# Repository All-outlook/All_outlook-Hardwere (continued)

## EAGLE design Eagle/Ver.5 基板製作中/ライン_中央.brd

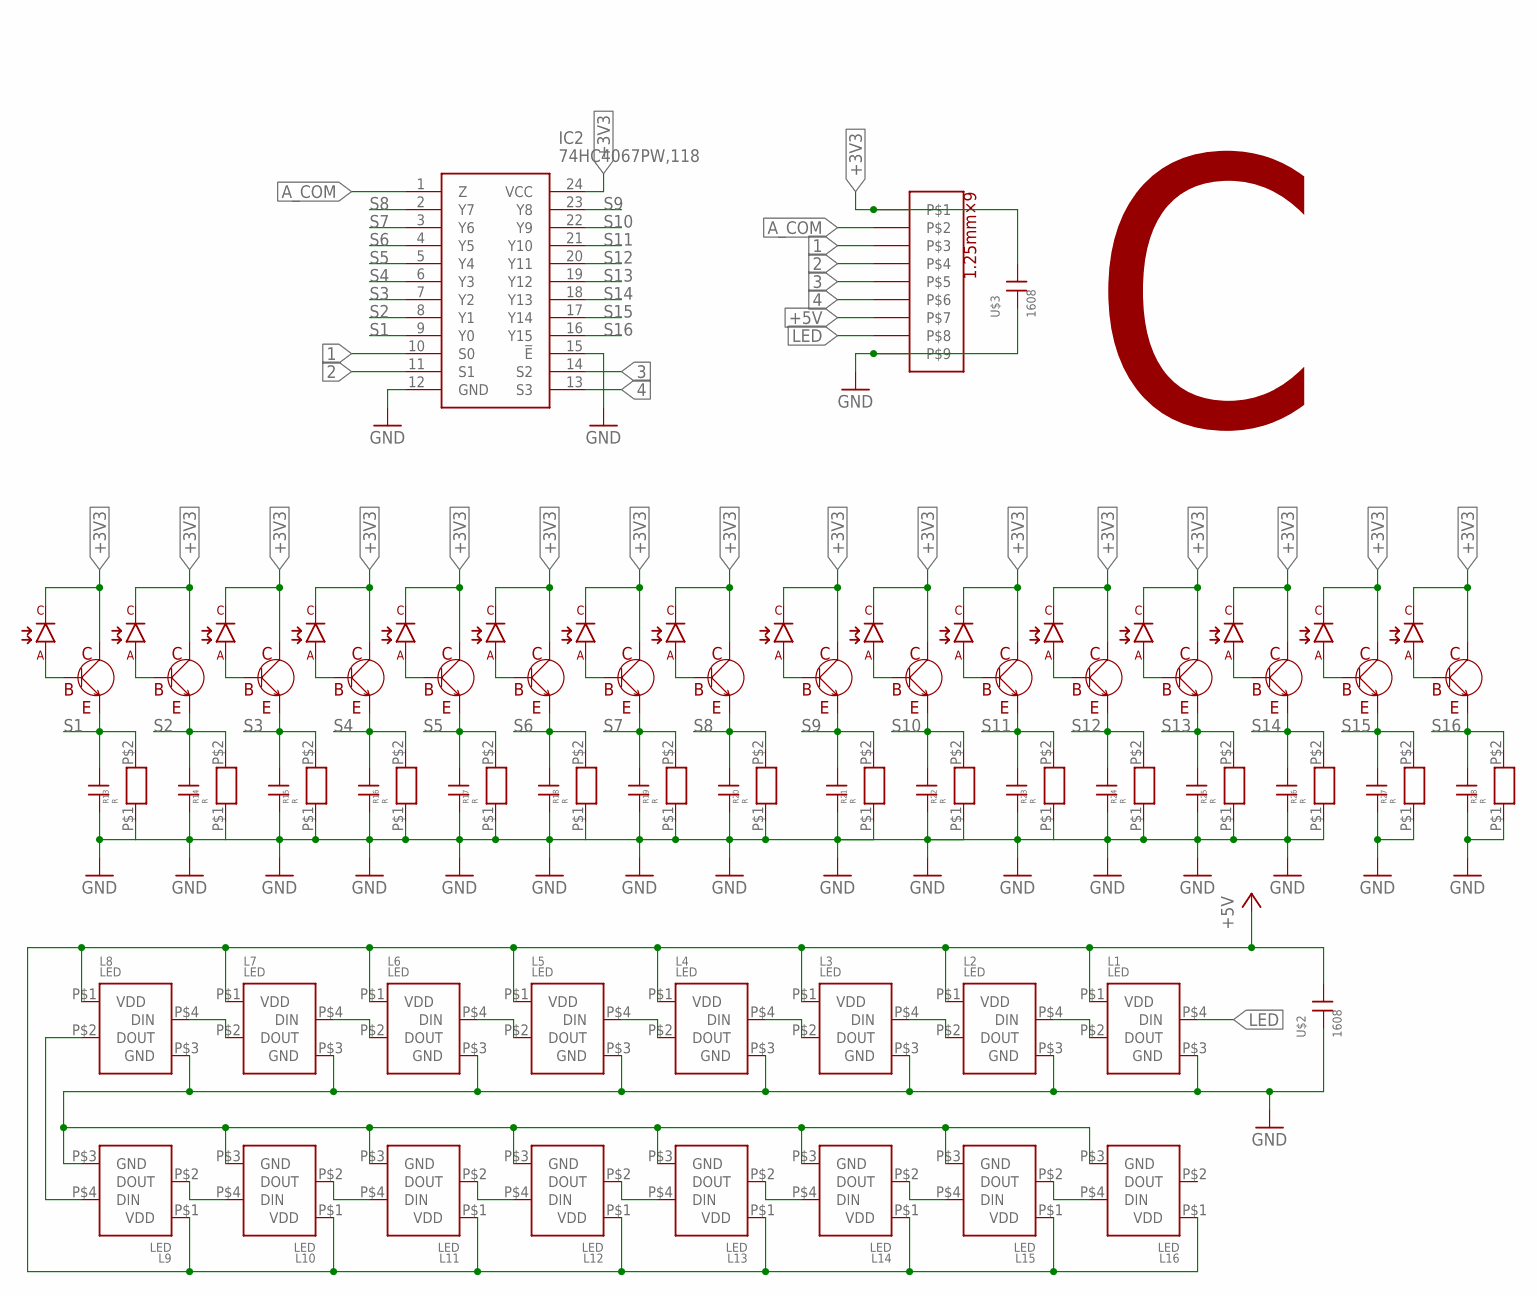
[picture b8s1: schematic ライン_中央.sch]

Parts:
C13, C14, C15, C16, C17, C18, C19, C20, C21, C22, C23, C24, C25, C26, C27, C28: 1608; CON
IC2: 74HC4067PW,118; SOP65P640X110-24N
L1, L2, L3, L4, L5, L6, L7, L8, L9, L10, L11, L12, L13, L14, L15, L16: LED
P1, P2, P3, P4, P5, P6, P7, P8, P9, P10, P11, P12, P13, P14, P15, P16: フォトダイオード
R13, R14, R15, R16, R17, R18, R19, R20, R21, R22, R23, R24, R25, R26, R27, R28: R; 1608
T1, T2, T3, T4, T5, T6, T7, T8, T9, T10, T11, T12, T13, T14, T15, T16: 2CS2712; TRANS_SSM3J325F,LF
U$1: 1MMCON
U$2, U$3: 1608; CON

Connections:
1: IC2.10 (S0), U$1.P$3
2: IC2.11 (S1), U$1.P$4
3: IC2.14 (S2), U$1.P$5
4: IC2.13 (S3), U$1.P$6
+3V3: IC2.24 (VCC), P1.C, P2.C, P3.C, P4.C, P5.C, P6.C, P7.C, P8.C, P9.C, P10.C, P11.C, P12.C, P13.C, P14.C, P15.C, P16.C, T1.C, T2.C, T3.C, T4.C, T5.C, T6.C, T7.C, T8.C, T9.C, T10.C, T11.C, T12.C, T13.C, T14.C, T15.C, T16.C, U$1.P$1, U$3.P$1 (1)
+5V: L1.P$1 (VDD), L2.P$1 (VDD), L3.P$1 (VDD), L4.P$1 (VDD), L5.P$1 (VDD), L6.P$1 (VDD), L7.P$1 (VDD), L8.P$1 (VDD), L9.P$1 (VDD), L10.P$1 (VDD), L11.P$1 (VDD), L12.P$1 (VDD), L13.P$1 (VDD), L14.P$1 (VDD), L15.P$1 (VDD), L16.P$1 (VDD), U$1.P$7, U$2.P$1 (1)
A_COM: IC2.1 (Z), U$1.P$2
GND: C13.P$2 (2), C14.P$2 (2), C15.P$2 (2), C16.P$2 (2), C17.P$2 (2), C18.P$2 (2), C19.P$2 (2), C20.P$2 (2), C21.P$2 (2), C22.P$2 (2), C23.P$2 (2), C24.P$2 (2), C25.P$2 (2), C26.P$2 (2), C27.P$2 (2), C28.P$2 (2), IC2.12 (GND), IC2.15 (!E), L1.P$3 (GND), L2.P$3 (GND), L3.P$3 (GND), L4.P$3 (GND), L5.P$3 (GND), L6.P$3 (GND), L7.P$3 (GND), L8.P$3 (GND), L9.P$3 (GND), L10.P$3 (GND), L11.P$3 (GND), L12.P$3 (GND), L13.P$3 (GND), L14.P$3 (GND), L15.P$3 (GND), L16.P$3 (GND), R13.P$1, R14.P$1, R15.P$1, R16.P$1, R17.P$1, R18.P$1, R19.P$1, R20.P$1, R21.P$1, R22.P$1, R23.P$1, R24.P$1, R25.P$1, R26.P$1, R27.P$1, R28.P$1, U$1.P$9, U$2.P$2 (2), U$3.P$2 (2)
LED: L1.P$4 (DIN), U$1.P$8
unnamed: P1.A, T1.B
unnamed: P2.A, T2.B
unnamed: P3.A, T3.B
unnamed: P4.A, T4.B
unnamed: P5.A, T5.B
unnamed: P6.A, T6.B
unnamed: P7.A, T7.B
unnamed: P8.A, T8.B
unnamed: P9.A, T9.B
unnamed: P10.A, T10.B
unnamed: P11.A, T11.B
unnamed: P12.A, T12.B
unnamed: P13.A, T13.B
unnamed: P14.A, T14.B
unnamed: P15.A, T15.B
unnamed: P16.A, T16.B
unnamed: L15.P$2 (DOUT), L16.P$4 (DIN)
unnamed: L14.P$2 (DOUT), L15.P$4 (DIN)
unnamed: L11.P$2 (DOUT), L12.P$4 (DIN)
unnamed: L10.P$2 (DOUT), L11.P$4 (DIN)
unnamed: L9.P$2 (DOUT), L10.P$4 (DIN)
unnamed: L13.P$2 (DOUT), L14.P$4 (DIN)
unnamed: L12.P$2 (DOUT), L13.P$4 (DIN)
unnamed: L7.P$2 (DOUT), L8.P$4 (DIN)
unnamed: L6.P$2 (DOUT), L7.P$4 (DIN)
unnamed: L3.P$2 (DOUT), L4.P$4 (DIN)
unnamed: L2.P$2 (DOUT), L3.P$4 (DIN)
unnamed: L1.P$2 (DOUT), L2.P$4 (DIN)
unnamed: L5.P$2 (DOUT), L6.P$4 (DIN)
unnamed: L4.P$2 (DOUT), L5.P$4 (DIN)
unnamed: L8.P$2 (DOUT), L9.P$4 (DIN)
S1: C13.P$1 (1), IC2.9 (Y0), R13.P$2, T1.E
S2: C14.P$1 (1), IC2.8 (Y1), R14.P$2, T2.E
S3: C15.P$1 (1), IC2.7 (Y2), R15.P$2, T3.E
S4: C16.P$1 (1), IC2.6 (Y3), R16.P$2, T4.E
S5: C17.P$1 (1), IC2.5 (Y4), R17.P$2, T5.E
S6: C18.P$1 (1), IC2.4 (Y5), R18.P$2, T6.E
S7: C19.P$1 (1), IC2.3 (Y6), R19.P$2, T7.E
S8: C20.P$1 (1), IC2.2 (Y7), R20.P$2, T8.E
S9: C21.P$1 (1), IC2.23 (Y8), R21.P$2, T9.E
S10: C22.P$1 (1), IC2.22 (Y9), R22.P$2, T10.E
S11: C23.P$1 (1), IC2.21 (Y10), R23.P$2, T11.E
S12: C24.P$1 (1), IC2.20 (Y11), R24.P$2, T12.E
S13: C25.P$1 (1), IC2.19 (Y12), R25.P$2, T13.E
S14: C26.P$1 (1), IC2.18 (Y13), R26.P$2, T14.E
S15: C27.P$1 (1), IC2.17 (Y14), R27.P$2, T15.E
S16: C28.P$1 (1), IC2.16 (Y15), R28.P$2, T16.E

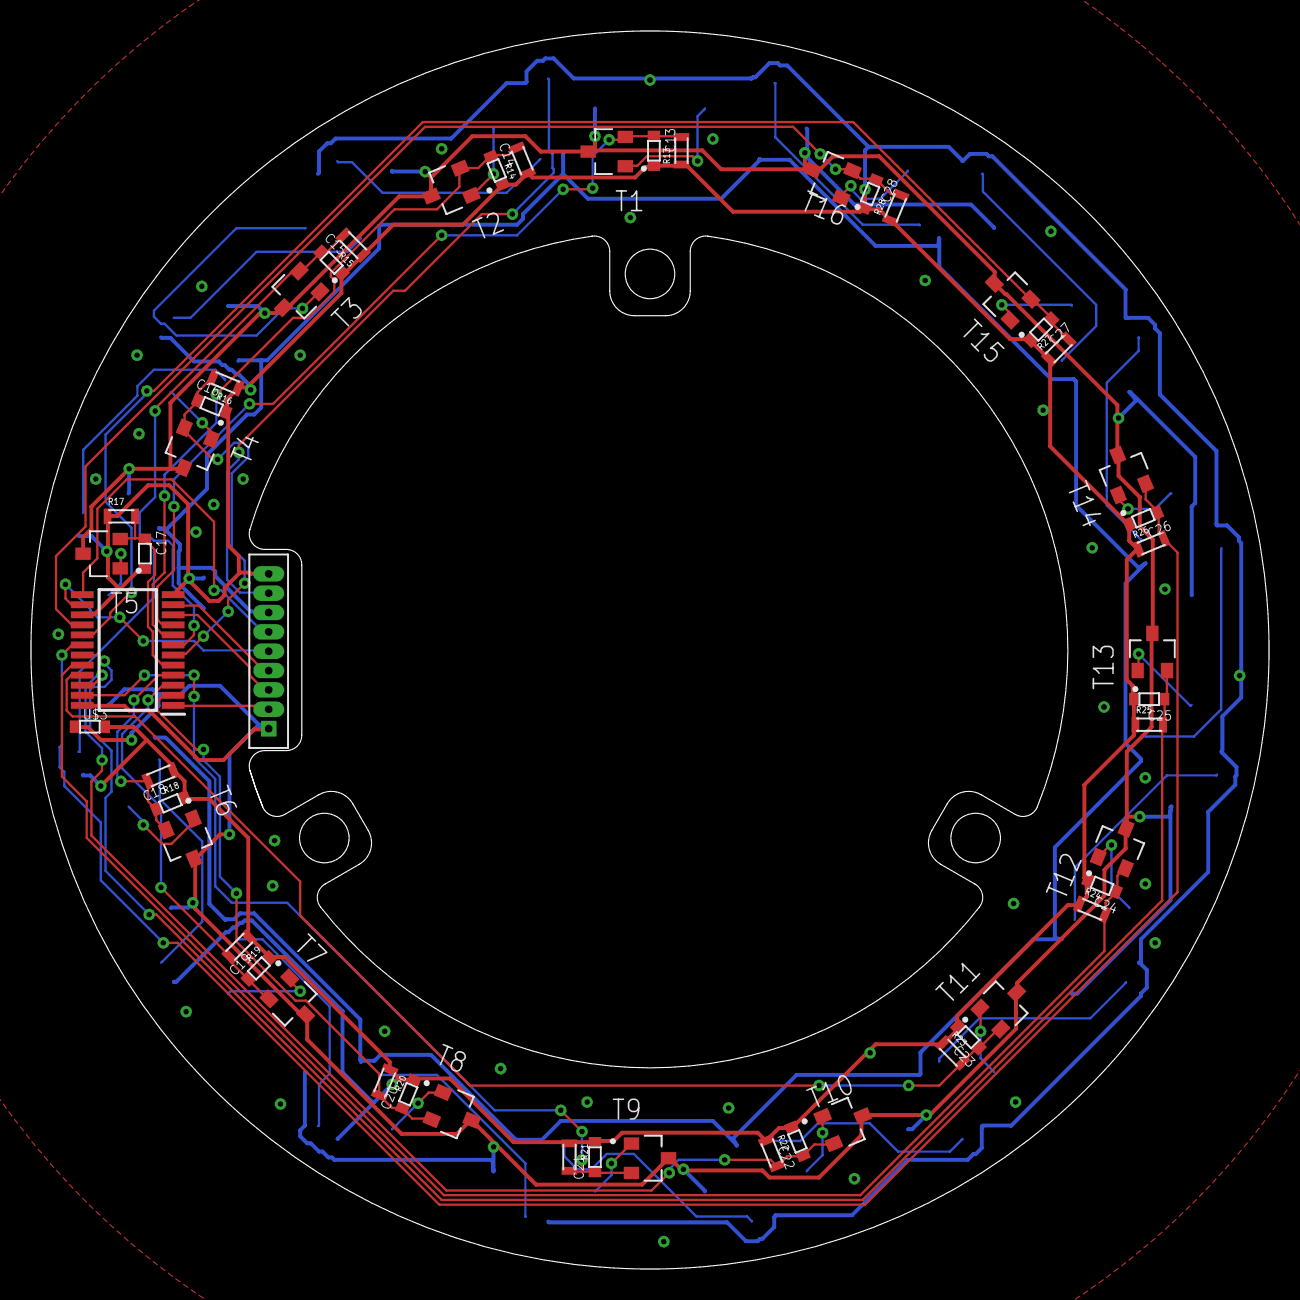
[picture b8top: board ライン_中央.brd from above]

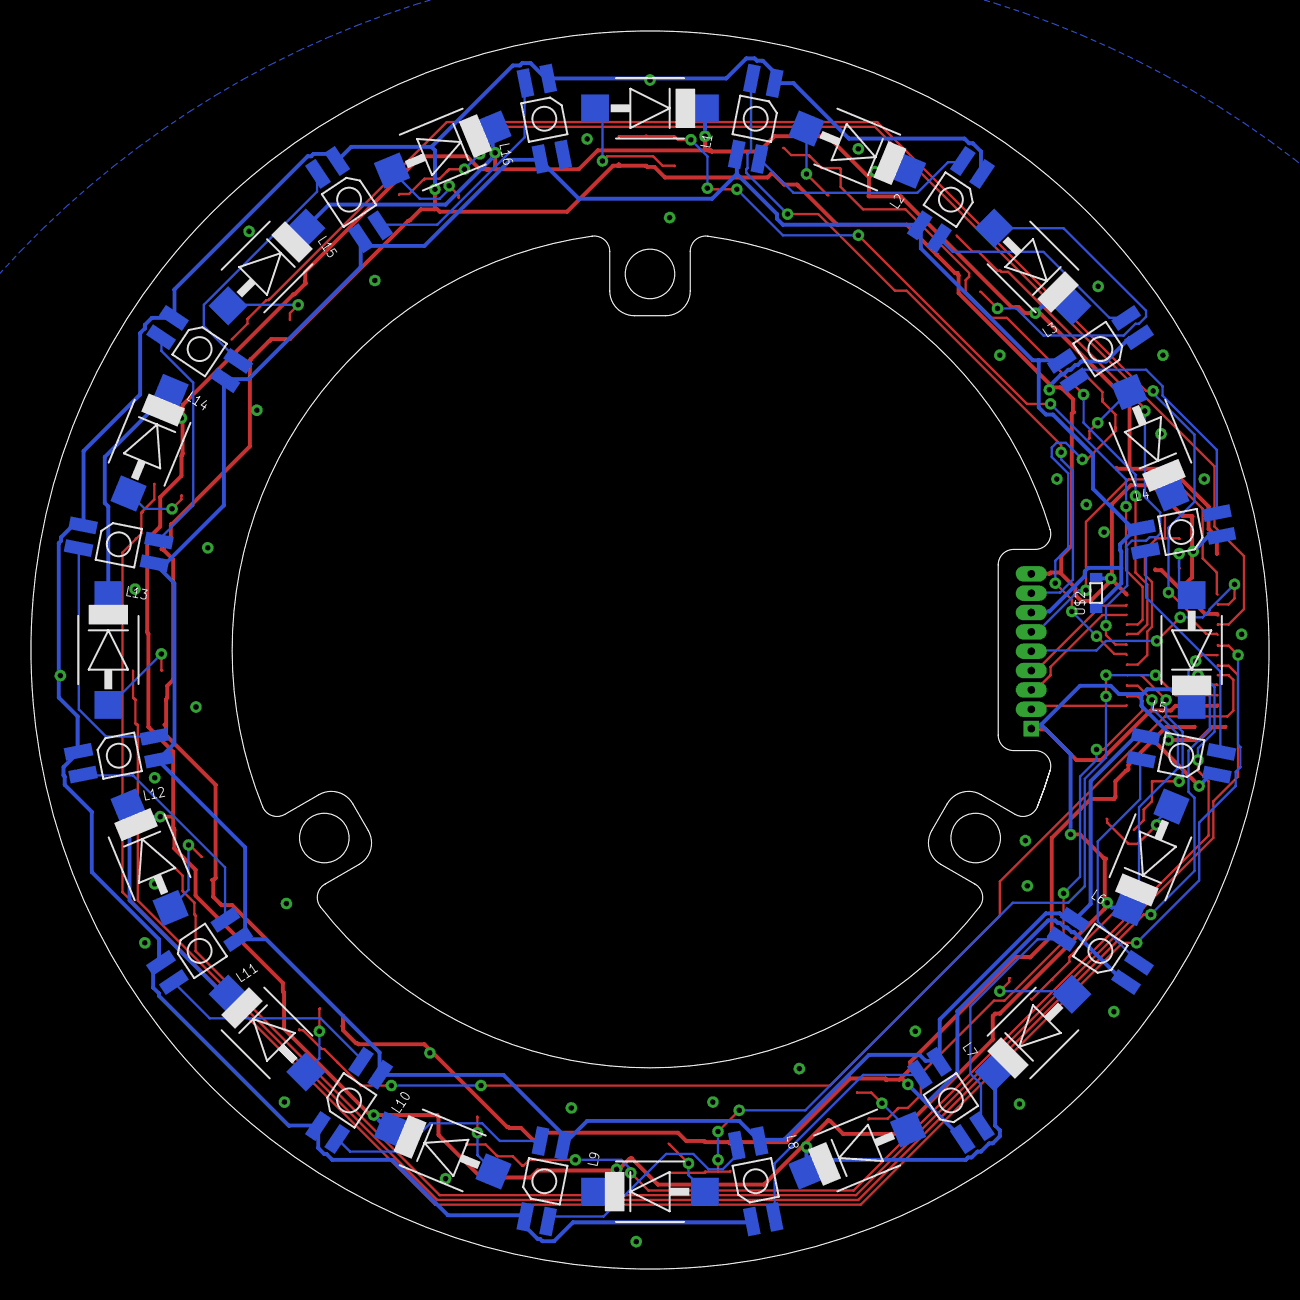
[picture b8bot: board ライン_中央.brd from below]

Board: 2 copper layers, 80.0 x 80.0 mm, 84 parts (33 on the bottom side), 56 nets.

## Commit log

2021-12-20 フレームの３Dプリンタデータ
2021-12-20 Eagle追加
    Eagleファイル作成
2021-12-20 ３Dパーツファイル追加
2021-12-28 こうしん
